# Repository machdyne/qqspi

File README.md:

# QQSPI Pmod&trade; compatible module

The QQSPI module provides access to four Quad SPI devices via a 12-pin Pmod&trade; compatible interface.

This repo contains schematics, pinouts and example Verilog code for the LD-QQSPI-PSRAM32 module.

Find more information on the [LD-QQSPI-PSRAM32 product page](https://machdyne.com/product/qqspi-psram32/).

## Modes

| PMOD/SS | PMODCS0 | PMODCS1 | -> | QSPI1/CE | QSPI2/CE | QSPI3/CE | QSPI4/CE |
| ------- | ------- | ------- | -- | -------- | -------- | -------- | -------- |
| H | X | X | -> | H | H | H | H |
| L | L | L | -> | L | H | H | H |
| L | H | L | -> | H | L | H | H |
| L | L | H | -> | H | H | L | H |
| L | H | H | -> | H | H | H | L |

## Pinout

| Pin | Signal |
| --- | ------ |
| 1 | /SS (active low) |
| 2 | SIO0 (MOSI) |
| 3 | SIO1 (MISO) |
| 4 | SCK |
| 5 | GND |
| 6 | 3V3 |
| 7 | SIO2 |
| 8 | SIO3 |
| 9 | CS0 |
| 10 | CS1 |
| 11 | GND |
| 12 | 3V3 |

## License

The contents of this repo are released under the [Lone Dynamics Open License](LICENSE.md) with the following exceptions:

- The KiCad design files contain parts of the [kicad-pmod](https://github.com/mithro/kicad-pmod) library which is released under the [Apache License, Version 2.0](https://www.apache.org/licenses/LICENSE-2.0.html).

- The KiCad design files may contain symbols and footprints released under other licenses; please contact us if we've failed to give proper attribution.

Note: You can use these designs for commercial purposes but we ask that instead of producing exact clones, that you either replace our trademarks and logos with your own or add your own next to ours.

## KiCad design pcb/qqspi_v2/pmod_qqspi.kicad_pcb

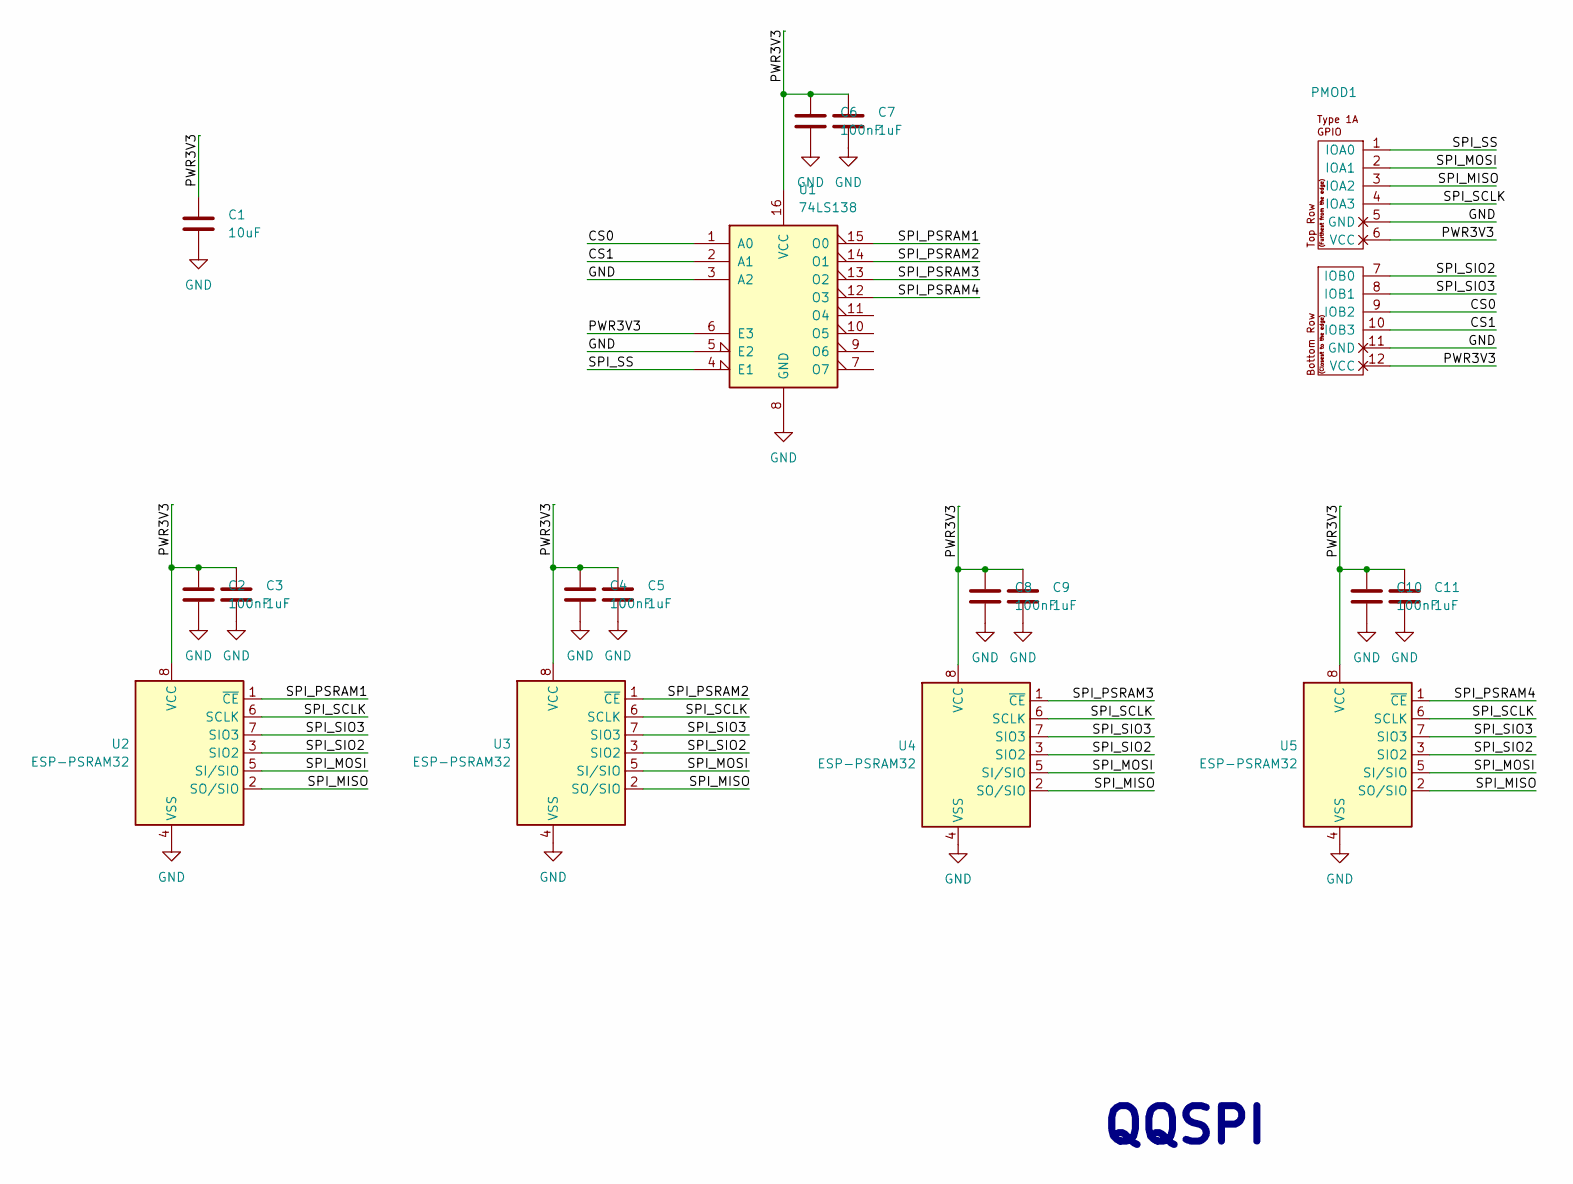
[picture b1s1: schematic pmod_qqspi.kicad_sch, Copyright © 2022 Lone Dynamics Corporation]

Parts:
C1: 10uF; C_0603_1608Metric
C2, C4, C6, C8, C10: 100nF; C_0603_1608Metric
C3, C5, C7, C9, C11: 1uF; C_0603_1608Metric
PMOD1: PMOD-Device-x2-Type-1A-GPIO; pmod_pin_array_6x2
U1: 74LS138; TSSOP-16_4.4x5mm_P0.65mm
U2, U3, U4, U5: ESP-PSRAM32; SOIC-8_3.9x4.9mm_P1.27mm

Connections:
/CS0: PMOD1.9 (IOB2), U1.1 (A0)
/CS1: PMOD1.10 (IOB3), U1.2 (A1)
/PWR3V3: C1.1, C2.1, C3.1, C4.1, C5.1, C6.1, C7.1, C8.1, C9.1, C10.1, C11.1, PMOD1.6 (VCC), PMOD1.12 (VCC), U1.6 (E3), U1.16 (VCC), U2.8 (VCC), U3.8 (VCC), U4.8 (VCC), U5.8 (VCC)
/SPI_MISO: PMOD1.3 (IOA2), U2.2 (SO/SIO), U3.2 (SO/SIO), U4.2 (SO/SIO), U5.2 (SO/SIO)
/SPI_MOSI: PMOD1.2 (IOA1), U2.5 (SI/SIO), U3.5 (SI/SIO), U4.5 (SI/SIO), U5.5 (SI/SIO)
/SPI_PSRAM1: U1.15 (O0), U2.1 (~CE)
/SPI_PSRAM2: U1.14 (O1), U3.1 (~CE)
/SPI_PSRAM3: U1.13 (O2), U4.1 (~CE)
/SPI_PSRAM4: U1.12 (O3), U5.1 (~CE)
/SPI_SCLK: PMOD1.4 (IOA3), U2.6 (SCLK), U3.6 (SCLK), U4.6 (SCLK), U5.6 (SCLK)
/SPI_SIO2: PMOD1.7 (IOB0), U2.3 (SIO2), U3.3 (SIO2), U4.3 (SIO2), U5.3 (SIO2)
/SPI_SIO3: PMOD1.8 (IOB1), U2.7 (SIO3), U3.7 (SIO3), U4.7 (SIO3), U5.7 (SIO3)
/SPI_SS: PMOD1.1 (IOA0), U1.4 (E1)
GND: C1.2, C2.2, C3.2, C4.2, C5.2, C6.2, C7.2, C8.2, C9.2, C10.2, C11.2, PMOD1.5 (GND), PMOD1.11 (GND), U1.3 (A2), U1.5 (E2), U1.8 (GND), U2.4 (VSS), U3.4 (VSS), U4.4 (VSS), U5.4 (VSS)

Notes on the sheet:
QQSPI

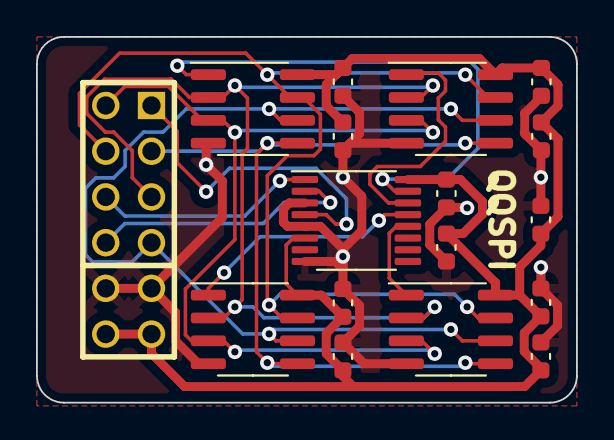
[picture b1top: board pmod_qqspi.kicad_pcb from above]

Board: 2 copper layers, 30.0 x 20.3 mm, 17 parts (0 on the bottom side), 14 nets.

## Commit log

2022-01-16 fix indentation
2022-02-19 added byte, halfword, word store operation via [3:0] wstrb and removed some verilator linter warnings
2022-03-25 add v2 schematics
2022-03-25 add image
2022-03-25 add image to readme
2023-09-14 add pcb layout
